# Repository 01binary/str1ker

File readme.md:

# Str1ker: The Drumming Mech

> [Str1ker](https://www.01binary.us/projects/drumming-robot/) is a human size, open-source mech integrated with Robot Operating System.

## Overview

Striker is a human-scale teleoperated mech built with metal casting, CNC machining, 3D printing, sheet metal parts, tube frame chassis, and pre-made components.

This open-source educational project features custom electronics and [Robot Operating System](https://www.ros.org/) integration, demonstrating how to design and build a large robot that combines mobility, sensing, and manipulation.

> See the [presentation](https://docs.google.com/presentation/d/125Y3McedITN_gVbnEh7SqTWY80QppUtimkaTmMLYEUg/edit?usp=sharing) about the robot at August 2026 [Portland Area Robotics Society](https://portlandrobotics.org/home.php?link_id=1) meeting.

| | | |
|-|-|-|
||||

The robot moves on a mecanum base, articulates its head and arms, and visualizes live lidar and RGB-D perception in Robot Visualization tool ([RViz](https://wiki.ros.org/rviz/Tutorials)).

The arms terminate in percussive end-effectors, designed for future live drum performance.

More details on [my blog](https://www.01binary.us/projects/drumming-robot/) and media on [instagram](https://www.instagram.com/01binaryus/). Say hello at the next [Portland Area Robotics Society](https://portlandrobotics.org/home.php?link_id=1) monthly meetup!

## Details

### Mechanical Design

[Autodesk Inventor mechanical parts](./cad) available in `./cad`.

### Electrical Design

[KiCad schematics and boards](./boards/) available in `./boards`.

### Fabrication

The arms were cast out of Aluminum 356 in the metal foundry at [Ctrl^H Hackerspace](https://pdxhackerspace.org/index.html) and welded together by [skorndaap](https://www.instagram.com/skorndaap/), then polished.

Tube frame chassis welding by [skorndaap](https://www.instagram.com/skorndaap/).

The CNC, sheet metal, tube frame, and 3D-printed parts were ordered from [Xometry](https://www.xometry.com/) online service.

The PCB's were ordered from [JLCPCB](https://jlcpcb.com/) using JLCPCB KiCad plugin.

Pre-made components sourced from [GoBilda](https://www.gobilda.com/), [Pololu](https://www.pololu.com/), [McMaster-Carr](https://www.mcmaster.com/), [Robot Shop](https://www.robotshop.com/), and Amazon.

### Software

- [Ubuntu 20.04](https://wiki.ros.org/noetic/Installation/Ubunt)
- [ROS Noetic](https://wiki.ros.org/noetic)
- [MoveIt](https://moveit.ai/)
- [ROS Control](./src/hardware/hardware.h)
- [Inverse Kinematics solver](./src/plugins/)
- [PID controller](./src/drivers/arm/pid.h)
- [ROS](./src) and [ROS Serial](./src/drivers/) nodes

### Hardware

- [Teensy 4.0](https://www.sparkfun.com/teensy-4-0.html) MCUs for arms, body and legs
- [Weidian](https://www.amazon.com/dp/B0BTVN6V7W) industrial mini PC for high-level control
- [Intel NUC 11](https://www.amazon.com/dp/B09PRL9V2F) for teleoperation & simulation

## System Requirements

The high-level controllers (Ubuntu 20.04/ROS Noetic) can run on any [mini PC](https://www.amazon.com/s?k=mini+pc), [NUC](https://www.amazon.com/s?k=NUC), a low-end Single Board Computer (SBC) like [Raspberry Pi](https://www.amazon.com/Raspberry-Model-2019-Quad-Bluetooth/dp/B07TD43PDZ/) or a high-end SBC like [Latte Panda 3 Delta](https://www.amazon.com/LattePanda-864-Pocket-Sized-Windows-Single-Computer/dp/B0C6TCP3MN).

The low-level serial nodes that run motors and sensors were designed for Arduino Mega, and are currently being ported to [Teensy 4.0](https://www.sparkfun.com/teensy-4-0.html) because its more powerful specs make it a better choice for robotics.

Teleoperation and simulation requires 3D visualization software like [RViz](https://wiki.ros.org/rviz) and [Gazebo](https://gazebosim.org/home), which [like NVidia cards](https://wiki.ros.org/simulator_gazebo/SystemRequirements).

## Setup

Follow the [official guide](https://wiki.ros.org/noetic/Installation/Ubuntu) to install ROS Noetic and [configure the ROS environment](https://wiki.ros.org/ROS/Tutorials/InstallingandConfiguringROSEnvironment).

Clone the projects:

```
mkdir -p ~/catkin_ws/src
cd ~/catkin_ws/src

git clone https://github.com/01binary/str1ker.git
git clone https://github.com/01binary/str1ker_moveit_config.git

cd ./str1ker
git sparse-checkout init --cone
git sparse-checkout set .vscode src config launch description msg
```

## Install Packages from Source

Follow the [official guide](https://moveit.ai/install/source/) to build MoveIt from source using `catkin_ws` as the workspace name instead of `moveit_ws`.

Prepare Gazebo plugins to be built from source:

```
cd ~/catkin_ws/src
git clone https://github.com/roboticsgroup/roboticsgroup_gazebo_plugins
```

## Install Packages

```
cd ~/catkin_ws/src
rosdep install -y --from-paths . --ignore-src --rosdistro noetic
```

## Build

To invoke the build command while in `~/catkin_ws` use `catkin_make` with no parameters. Otherwise use `-C` to specify the workspace directory:

```
catkin_make -C ~/catkin_ws
```

To build only this package and its dependencies:

```
catkin_make --only-pkg-with-deps str1ker
```

To build only this package:

```
catkin_make --pkg str1ker
```

To clear the build filter:

```
catkin_make -DCATKIN_WHITELIST_PACKAGES=""
```

To switch between Debug and Release

```
catkin_make -DCMAKE_BUILD_TYPE=Debug | Release
```

## Environment

One-time setup after the first build.

```
catkin_make install
source /opt/ros/noetic/setup.bash

echo "source /opt/ros/noetic/setup.bash" >> ~/.bashrc
source ~/.bashrc
```

## Upload

The low-level hardware is handled by an Arduino ROS node in `src/drivers/arm.ino`.

To build it, first generate ROS message headers for Arduino:

```
sudo apt-get install ros-${ROS_DISTRO}-rosserial-arduino
sudo apt-get install ros-${ROS_DISTRO}-rosserial

rosrun rosserial_arduino make_libraries.py ~/Arduino/libraries
```

> If you installed Arduino IDE as a *snap* plugin, Arduino libraries are likely in `~/snap/arduino` (the exact location is specific to your system).

Compile and upload the ROS node. The default launch configuration in `robot.launch` will connect to `/dev/ttyACM0` automatically.

### VSCode + Arduino CLI

This workspace includes VSCode tasks for compiling and uploading the Teensy firmware without Arduino IDE 2.

Install `arduino-cli`:

```bash
curl -fsSL https://raw.githubusercontent.com/arduino/arduino-cli/master/install.sh | BINDIR="$HOME/.local/bin" sh
arduino-cli version
```

Then in VSCode:

1. Open the Command Palette and run `C/C++: Select a Configuration...`
2. Pick `Arduino Teensy 4.0`
3. Run `Tasks: Run Task`
4. Use `Arduino: Compile Arm` or `Arduino: Upload Arm`

The checked-in VSCode configuration targets `teensy:avr:teensy40` on `/dev/ttyACM0` and uses the PJRC package index through `.vscode/arduino-cli.yaml`.

## Launch

### Hardware

To launch only the serial bridge to the arm firmware:

```
roslaunch str1ker arms.launch
```

To launch only the serial bridge to the main board firmware:

```
roslaunch str1ker main.launch
```

### Controllers

To launch ROS control nodes (URDF + controllers + state publisher):

```
roslaunch str1ker controllers.launch
```

### Full Stack

To launch both high-level and low-level nodes:

```
roslaunch str1ker robot.launch
```

### PrimeSense Carmine 1.09

To launch Carmine with OpenNI2 (recommended on ROS Noetic):

```
roslaunch str1ker vision.launch
```

To use legacy OpenNI instead:

```
roslaunch str1ker vision.launch use_openni2:=false
```

### Laser Scanner (Hokuyo UTM-30LX)

Install the Hokuyo ROS driver:

```
sudo apt-get install -y ros-${ROS_DISTRO}-urg-node
```

The default launch path uses the stable built-in udev symlink under `/dev/serial/by-id`.

If you still want a custom short alias (for example `/dev/str1ker_laser`), create one with:

```
# Example when Hokuyo appears as /dev/ttyACM0
./scripts/alias.sh /dev/ttyACM0 str1ker_laser --install
```

To launch the laser scanner driver:

```
roslaunch str1ker laserscan.launch
```

If you want to bypass by-id and use the current kernel device path:

```
roslaunch str1ker laserscan.launch serial_port:=/dev/ttyACM0
```

### Mecanum Legs

The legs firmware runs as a rosserial Arduino node and subscribes to `cmd_vel`
using `geometry_msgs/Twist` (`linear.x`, `linear.y`, and `angular.z`).

To launch the serial bridge:

```
roslaunch str1ker legs.launch serial_port:=/dev/ttyACM0
```

Quick forward-motion smoke test:

```
rostopic pub -r 10 /cmd_vel geometry_msgs/Twist "{linear: {x: 0.2, y: 0.0, z: 0.0}, angular: {x: 0.0, y: 0.0, z: 0.0}}"
```

### Teleoperation

To teleoperate the robot:

```
roslaunch str1ker_moveit_config demo.launch
```

### Simulation

To simulate the robot:

```
roslaunch str1ker_moveit_config gazebo.launch
```

### Configuration

The low-level configuration is in YAML format at [config](./config/).

To launch the MoveIt wizard for custom robot arm setup:

```
roslaunch moveit_setup_assistant setup_assistant.launch
```

## Logging

Logging level can be specified in `$ROS_ROOT/config/rosconsole.config`, either globally or for a specific package.

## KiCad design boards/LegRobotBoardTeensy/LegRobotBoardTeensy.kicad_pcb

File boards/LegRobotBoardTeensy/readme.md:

# Leg Robot Board

A board that controls the mobile platform with four mecanum wheels:

+ Leg Actuators
+ Leg Actuator Potentiometers
+ Leg Wheels
+ Leg Wheel Encoders
+ 9-DOF IMU
+ Enabled and PWM activity LEDs
+ Wheel Speed 7-Segment LED Indicators

## Modules

The following components are placed onto the board as modules:

|Module|Function|
|-|-|
|[Teensy 4.1](https://www.pjrc.com/store/teensy41.html)|[ROS](https://www.ros.org/) Node|
|[Adafruit 9-DOF IMU](https://www.adafruit.com/product/2472)|[TF2](https://wiki.ros.org/tf2) Transform|

## Devices

The following external components are connected to the board via `JST-XH` locking connectors:

|Device|Function|
|-|-|
|8x [IBT2 Motor Drivers](https://www.amazon.com/2-Piece-High-Power-Limiting-Function-Suitable/dp/B0DXKXKYRK)|Wheel Motor Drivers, Leg Actuator Drivers (`8` pin IDC connector: `3V3`, `GND`, `L_EN`, `R_EN`, `LPWM`, `RPWM`, `L_IS`, `R_IS`)|
|4x [Feedback Rod Linear Actuator](https://www.firgelliauto.com/products/feedback-rod-actuator?variant=2632742851) Potentiometers|Leg Actuator Potentiometers (`3` pin JST-XH connector: `3V3`, `SIG`, `GND`)|
|4x [Leg (Wheel) Encoder Board](../LegEncoderBoard/readme.md)|Wheel Encoders (`8` pin IDC connector: `A`, `B`, `I`, `3V3`, and four `GND`'s|

## Functionality

### PWM

There are four legs and each has two motors: a linear lift actuator and a brushed DC motor that runs the wheel.

Each PWM channel gets its own `EN` (Enabled) signal. The current sense signals (`L_IS`, `R_IS`) are included in the connector layout and sent over the wire, but not used anywhere on the board because there aren't enough pins for them. A multiplexer can be added later if the signals are desired.

### ADC

The linear lift actuators have built-in multi-turn potentiometers. These are routed to Teensy `ADC` pins.

### Quadrature

The [wheel encoders](../LegEncoderBoard/readme.md) are connected to each of the four wheels, outputting `A`, `B`, and `I` pulses counting rotations (`1000` pulses per revolution).

### Number Displays

Four 7-segment common anode LED number displays with decimal points display the speed of each wheel from `0.0` to `1.0`. They are driven by an LED multiplexer.

The LED multiplexer is mapped to four 2-digit LED displays with decimal point as follows:

| Display function                 | `IS31FL3730` pins |
| -------------------------------- | ----------------- |
| Digit common anodes              | `SW1–SW8`         |
| Segments A, B, C, D, E, F, G, DP | `CS1–CS8`         |

The [3621BH](https://www.amazon.com/uxcell-Common-Segment-Display-Digital/dp/B07GTRS9L2) common-anode LED displays have the following pin footprint:

| |1|2|3|4|5|
|-|-|-|-|-|-|
|1|`COM0`|`B`|`C`|`E`|`D`|
|2|`G`|`DP`|`A`|`F`|`COM1`|

The digit segments are mapped as follows:

|Digit|Segments
|-|-|
||`A` - Top of upper square<br>`F` - Left of upper square<br>`B` - Right of upper square<br>`G` - Link of both squares<br>`E` - Left of lower square<br>`C` - Right of lower square<br>`D` - Bottom of lower square<br>`DP` - Decimal point

## Pin Mapping

This board is essentially a shield. Labeled locking connectors are provided for all of the devices, PWM enabled/activity is indicated by LEDs, and wheel speeds are indicated by number displays.

| Pin            | Function                       | Group                     |
| -------------- | ------------------------------ | ------------------------- |
| `A16`          | Actuator 1 Potentiometer `SIG` | Front Left Leg (Actuator) |
| `D32`          | Quadrature Encoder 1 `A`       | Front Left Leg (Wheel)    |
| `D33`          | Quadrature Encoder 1 `B`       | Front Left Leg (Wheel)    |
| `D22`          | Quadrature Encoder 1 `Index`   | Front Left Leg (Wheel)    |
| `D26`          | Motor Driver 1 `EN`            | Front Left Leg (Wheel)    |
| `D27`          | Motor Driver 2 `EN`            | Front Left Leg (Actuator) |
| `D0`           | Motor Driver 1 `RPWM`          | Front Left Leg (Wheel)    |
| `D1`           | Motor Driver 1 `LPWM`          | Front Left Leg (Wheel)    |
| `D2`           | Motor Driver 2 `RPWM`          | Front Left Leg (Actuator) |
| `D3`           | Motor Driver 2 `LPWM`          | Front Left Leg (Actuator) |
| `A17`          | Actuator 2 Potentiometer `SIG` | Front Right Leg (Actuator)|
| `D34`          | Quadrature Encoder 2 `A`       | Front Right Leg (Wheel)   |
| `D35`          | Quadrature Encoder 2 `B`       | Front Right Leg (Wheel)   |
| `D23`          | Quadrature Encoder 2 `Index`   | Front Right Leg (Wheel)   |
| `D28`          | Motor Driver 3 `EN`            | Front Right Leg (Wheel)   |
| `D29`          | Motor Driver 4 `EN`            | Front Right Leg (Actuator)|
| `D4`           | Motor Driver 3 `RPWM`          | Front Right Leg (Wheel)   |
| `D5`           | Motor Driver 3 `LPWM`          | Front Right Leg (Wheel)   |
| `D6`           | Motor Driver 4 `RPWM`          | Front Right Leg (Actuator)|
| `D7`           | Motor Driver 4 `LPWM`          | Front Right Leg (Actuator)|
| `A2`           | Actuator 3 Potentiometer `SIG` | Rear Left Leg (Actuator)  |
| `D36`          | Quadrature Encoder 3 `A`       | Rear Left Leg (Wheel)     |
| `D37`          | Quadrature Encoder 3 `B`       | Rear Left Leg (Wheel)     |
| `D24`          | Quadrature Encoder 3 `Index`   | Rear Left Leg (Wheel)     |
| `D30`          | Motor Driver 5 `EN`            | Rear Left Leg (Wheel)     |
| `D31`          | Motor Driver 6 `EN`            | Rear Left Leg (Actuator)  |
| `D8`           | Motor Driver 5 `RPWM`          | Rear Left Leg (Wheel)     |
| `D9`           | Motor Driver 5 `LPWM`          | Rear Left Leg (Wheel)     |
| `D10`          | Motor Driver 6 `RPWM`          | Rear Left Leg (Actuator)  |
| `D11`          | Motor Driver 6 `LPWM`          | Rear Left Leg (Actuator)  |
| `A3`           | Actuator 4 Potentiometer `SIG` | Rear Right Leg (Actuator) |
| `D38`          | Quadrature Encoder 4 `A`       | Rear Right Leg (Wheel)    |
| `D39`          | Quadrature Encoder 4 `B`       | Rear Right Leg (Wheel)    |
| `D25`          | Quadrature Encoder 4 `Index`   | Rear Right Leg (Wheel)    |
| `D20`          | Motor Driver 7 `EN`            | Rear Right Leg (Wheel)    |
| `D21`          | Motor Driver 8 `EN`            | Rear Right Leg (Actuator) |
| `D12`          | Motor Driver 7 `RPWM`          | Rear Right Leg (Wheel)    |
| `D13`          | Motor Driver 7 `LPWM`          | Rear Right Leg (Wheel)    |
| `D14`          | Motor Driver 8 `RPWM`          | Rear Right Leg (Actuator) |
| `D15`          | Motor Driver 8 `LPWM`          | Rear Right Leg (Actuator) |
| `A5`           | I2C `SCL`                      | IMU, LED Driver           |
| `A4`           | I2C `SDA`                      | IMU, LED Driver           |

## Buses

|Device|Bus|Address
|-|-|-|
|IMU|I2C|`0x28` (`ADR` tied to `GND` to set address)|
|IS31FL3730|I2C|`0x74`|

## Bill of Materials

|Component|Description|
|-|-|
|[IS31FL3730](https://www.digikey.com/en/products/detail/lumissil-microsystems/IS31FL3730-QFLS2-TR/5319756)|LED Driver/Multiplexer
|[CL3621BH](https://www.amazon.com/dp/B07GTQTD8S)|LED Displays (2-Digit, 7-Segment, 10-Pin Common Anode) for Wheel Speeds
|[XL-1608SURC-06](https://www.lcsc.com/product-detail/C965799.html)|Red LED for `EN` signals|
|[150080BS75000](https://www.digikey.com/en/products/detail/w%C3%BCrth-elektronik/)|Blue LED for `LPWM`/`RPWM` signals|
|[RC0603FR-07150RL](https://www.digikey.com/en/products/detail/yageo/RC0603FR-07150RL/726958)|`150 Ohm` LED Resistor|
|[RC0603FR-07470RL](https://www.digikey.com/en/products/detail/yageo/RC0603FR-07470RL/727256)|`470R` Red LED Resistor|
|[RCG06031K00FKEA](https://www.digikey.com/en/products/detail/vishay-dale/rcg06031k00fkea/4172389)|`1K` LED Resistor|
|[RC0603FR-072K2L](https://www.digikey.com/en/products/detail/yageo/rc0603fr-072k2l/727016)|`2.2K` Series Resistor (ADC channels)|
|[CR0603-FX-4701ELF](https://www.digikey.com/en/products/detail/bourns-inc/cr0603-fx-4701elf/3740916)|`4.7K` Pull-Up Resistor for LED Multiplexer|
|[CRCW060310K0FKEA](https://www.digikey.com/en/products/detail/vishay-dale/crcw060310k0fkea/1174782)|`10K` 555 Timer Pull-Up Resistor, Transistor Base Resistor|
|[HoAR0603-1/10W-20KR-1%-TCR25](https://jlcpcb.com/partdetail/C5123585)|`20K` LED Driver Current Setting Resistor|
|[CRCW0603100KFKEA](https://www.digikey.com/en/products/detail/vishay-dale/crcw0603100kfkea/1174896)|`100K` Transistor Base Pull-Down Resistor|
|[RC0603FR-07360KL](https://www.digikey.com/en/products/detail/yageo/rc0603fr-07360kl/727183)|`360K` 555 Timer Resistor|
|[C0402C103J4RACTU](https://www.digikey.com/en/products/detail/kemet/C0402C103J4RACTU/411041)|`10nF` 555 Timer Capacitor|
|[CL10B473KB8NNNC](https://www.digikey.com/en/products/detail/samsung-electro-mechanics/cl10b473kb8nnnc/3886721)|`47nF` Decoupling Capacitor (ADC channels)|
|[CC0603KRX7R9BB104](https://www.digikey.com/en/products/detail/yageo/cc0603krx7r9bb104/2103082)|`100nF` IMU Capacitor|
|[CC0603JRX7R7BB105](https://www.digikey.com/en/products/detail/yageo/CC0603JRX7R7BB105/7164369)|`1uF` 555 Timer Capacitor|
|[SN74HC08DR](https://www.digikey.com/en/products/detail/texas-instruments/sn74hc08dr/276834)|IC Gate|
|[MMBT3904LT1G](https://www.digikey.com/en/products/detail/onsemi/MMBT3904LT1G/919601)|LED Transistor|
|[TLC555CDR](https://www.digikey.com/en/products/detail/texas-instruments/tlc555cdr/276979)|555 Timer|
|[JST_XH_B3B-XH-A](https://www.digikey.com/en/products/detail/jst-sales-america-inc/b3b-xh-a/1651046)|Actuator Potentiometers (`3V3`, `SIG`, `GND`)|
|[Molex 0702460802](https://www.digikey.com/en/products/detail/molex/0702460802/760180)|Motor Drivers (`LPWM`, `RPWM`, `L_EN`, `R_EN`, `L_IS`, `R_IS`, `3V3`, `GND`)|
|[Teensy 4.1](https://www.sparkfun.com/teensy-4-1.html)|Teensy 4.1 without Headers|
|[ICM-648-1-GT-HT](https://www.digikey.com/en/products/detail/adam-tech/ICM-648-1-GT-HT/9832918)|Teensy IC DIP Socket, 48P|
|[Needle Headers](https://www.amazon.com/dp/B09WH8N3HX)|Teensy Needle Headers for DIP Socket|
|[DIP Socket 10 pin](https://www.amazon.com/dp/B0FVDT8JGV)|LED number displays IC socket

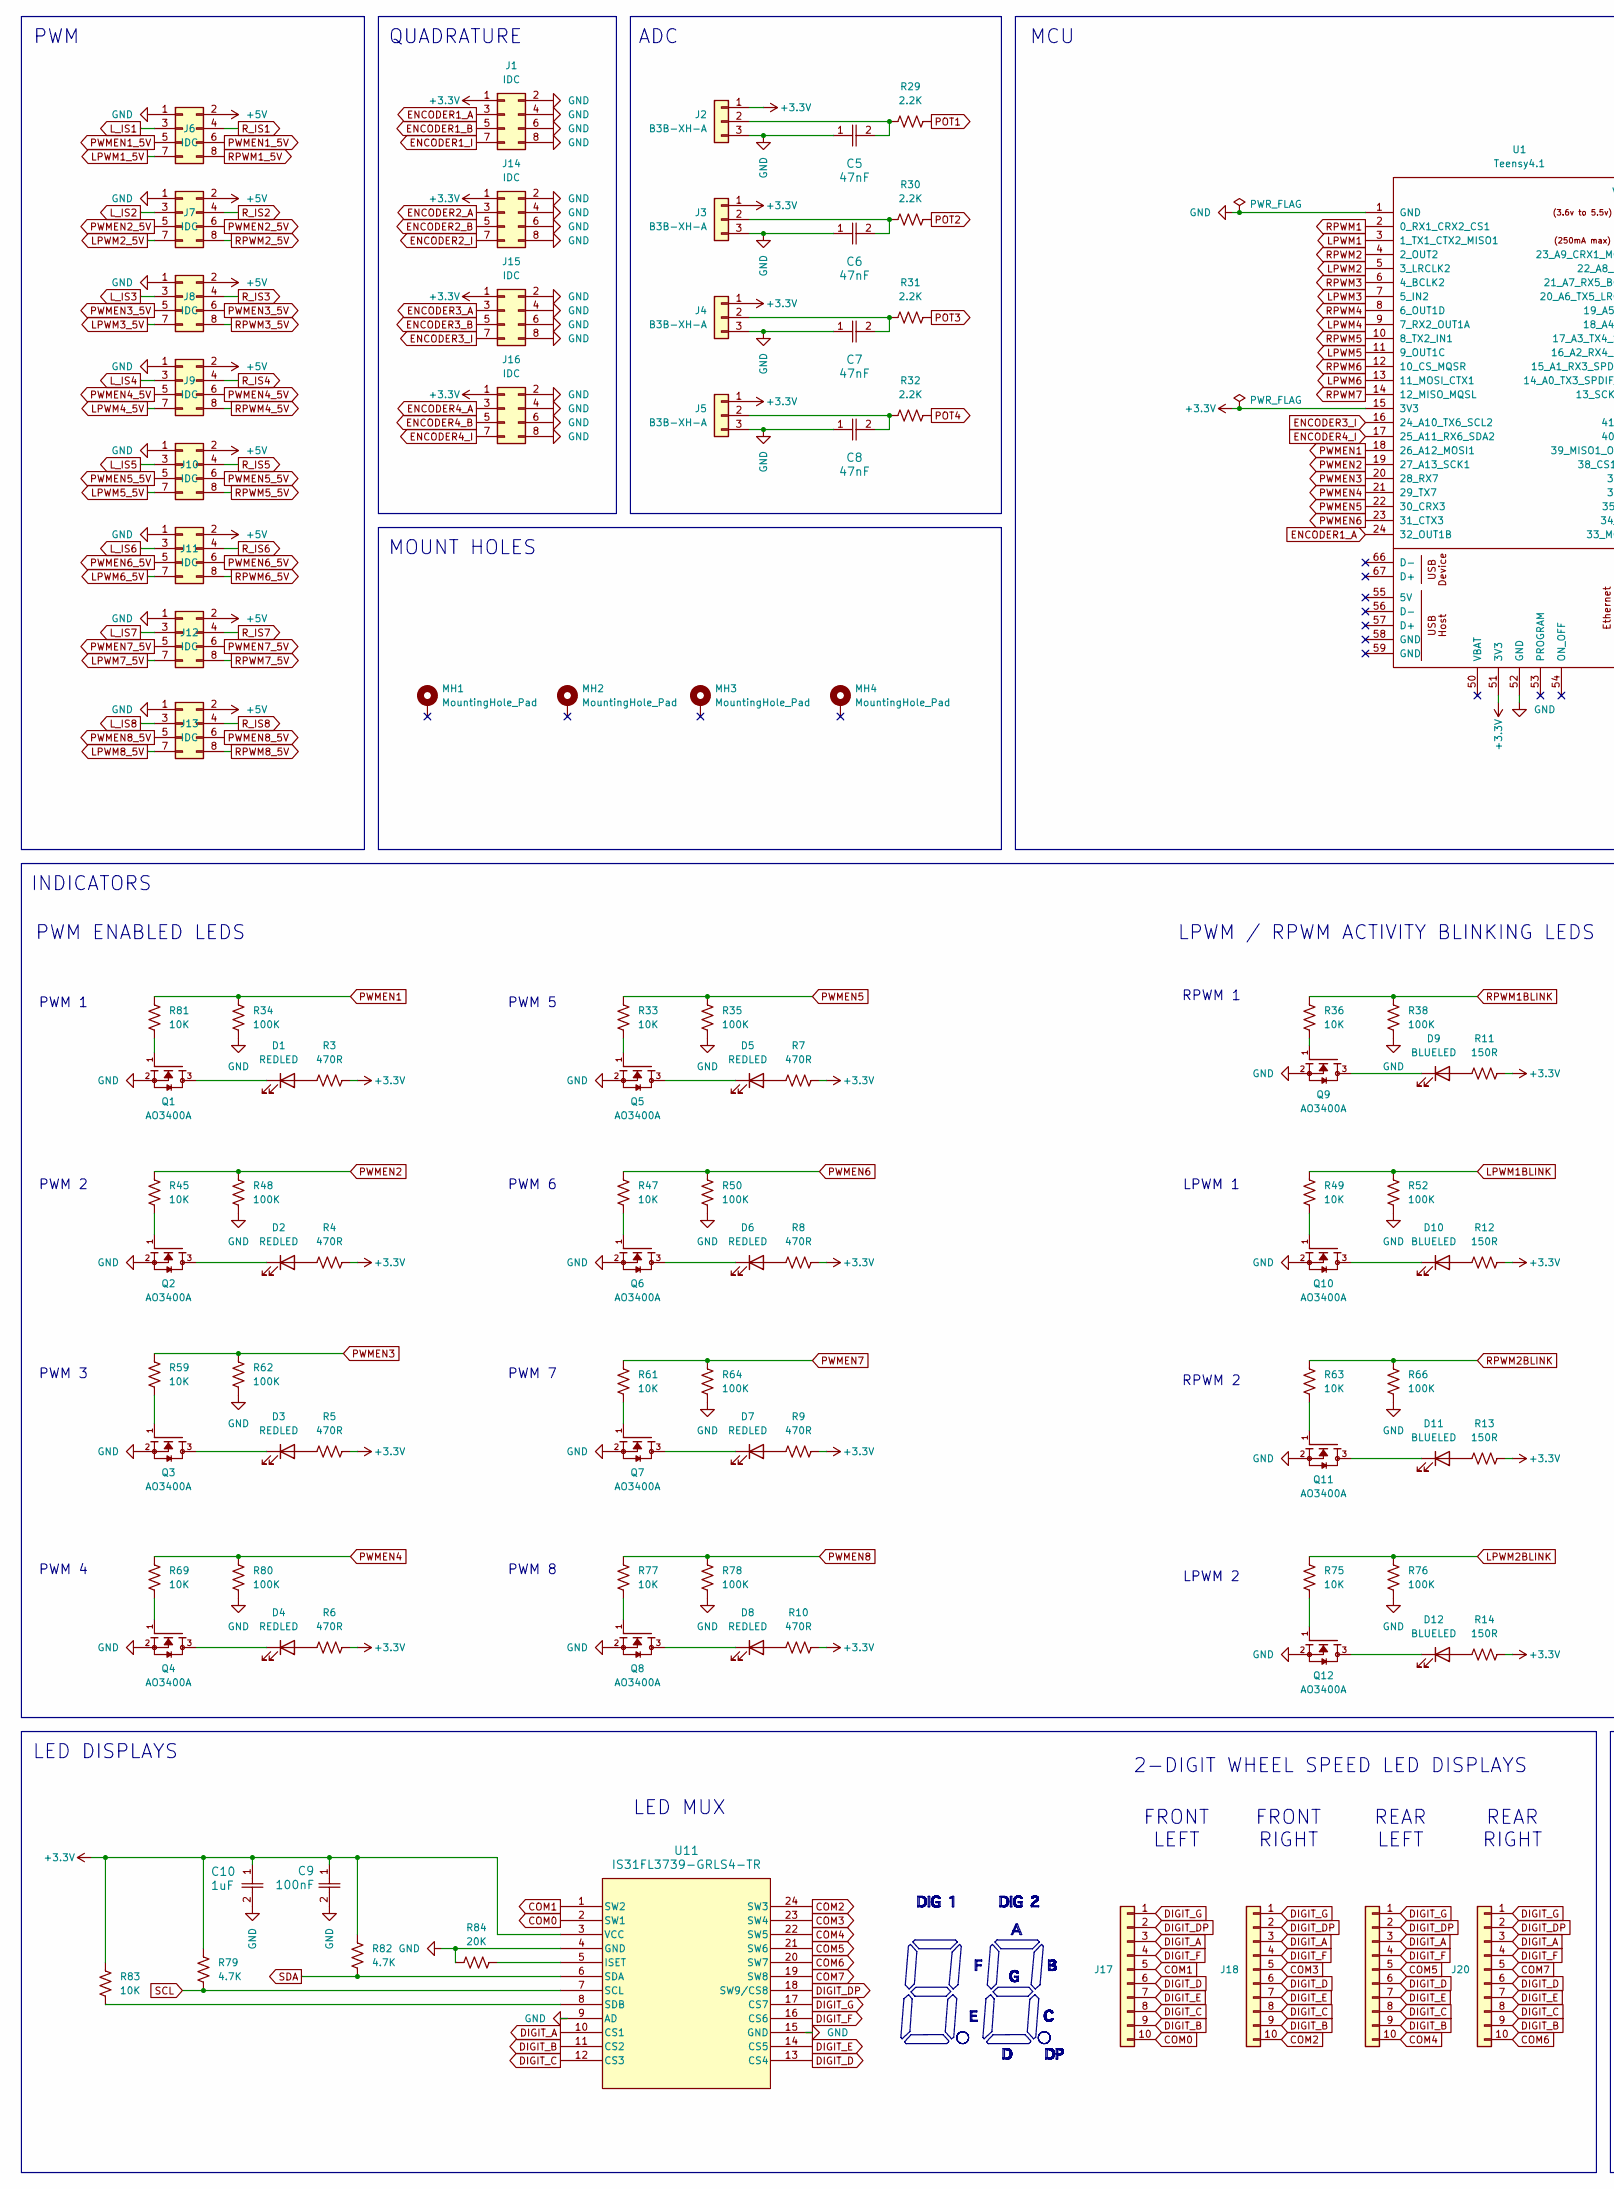
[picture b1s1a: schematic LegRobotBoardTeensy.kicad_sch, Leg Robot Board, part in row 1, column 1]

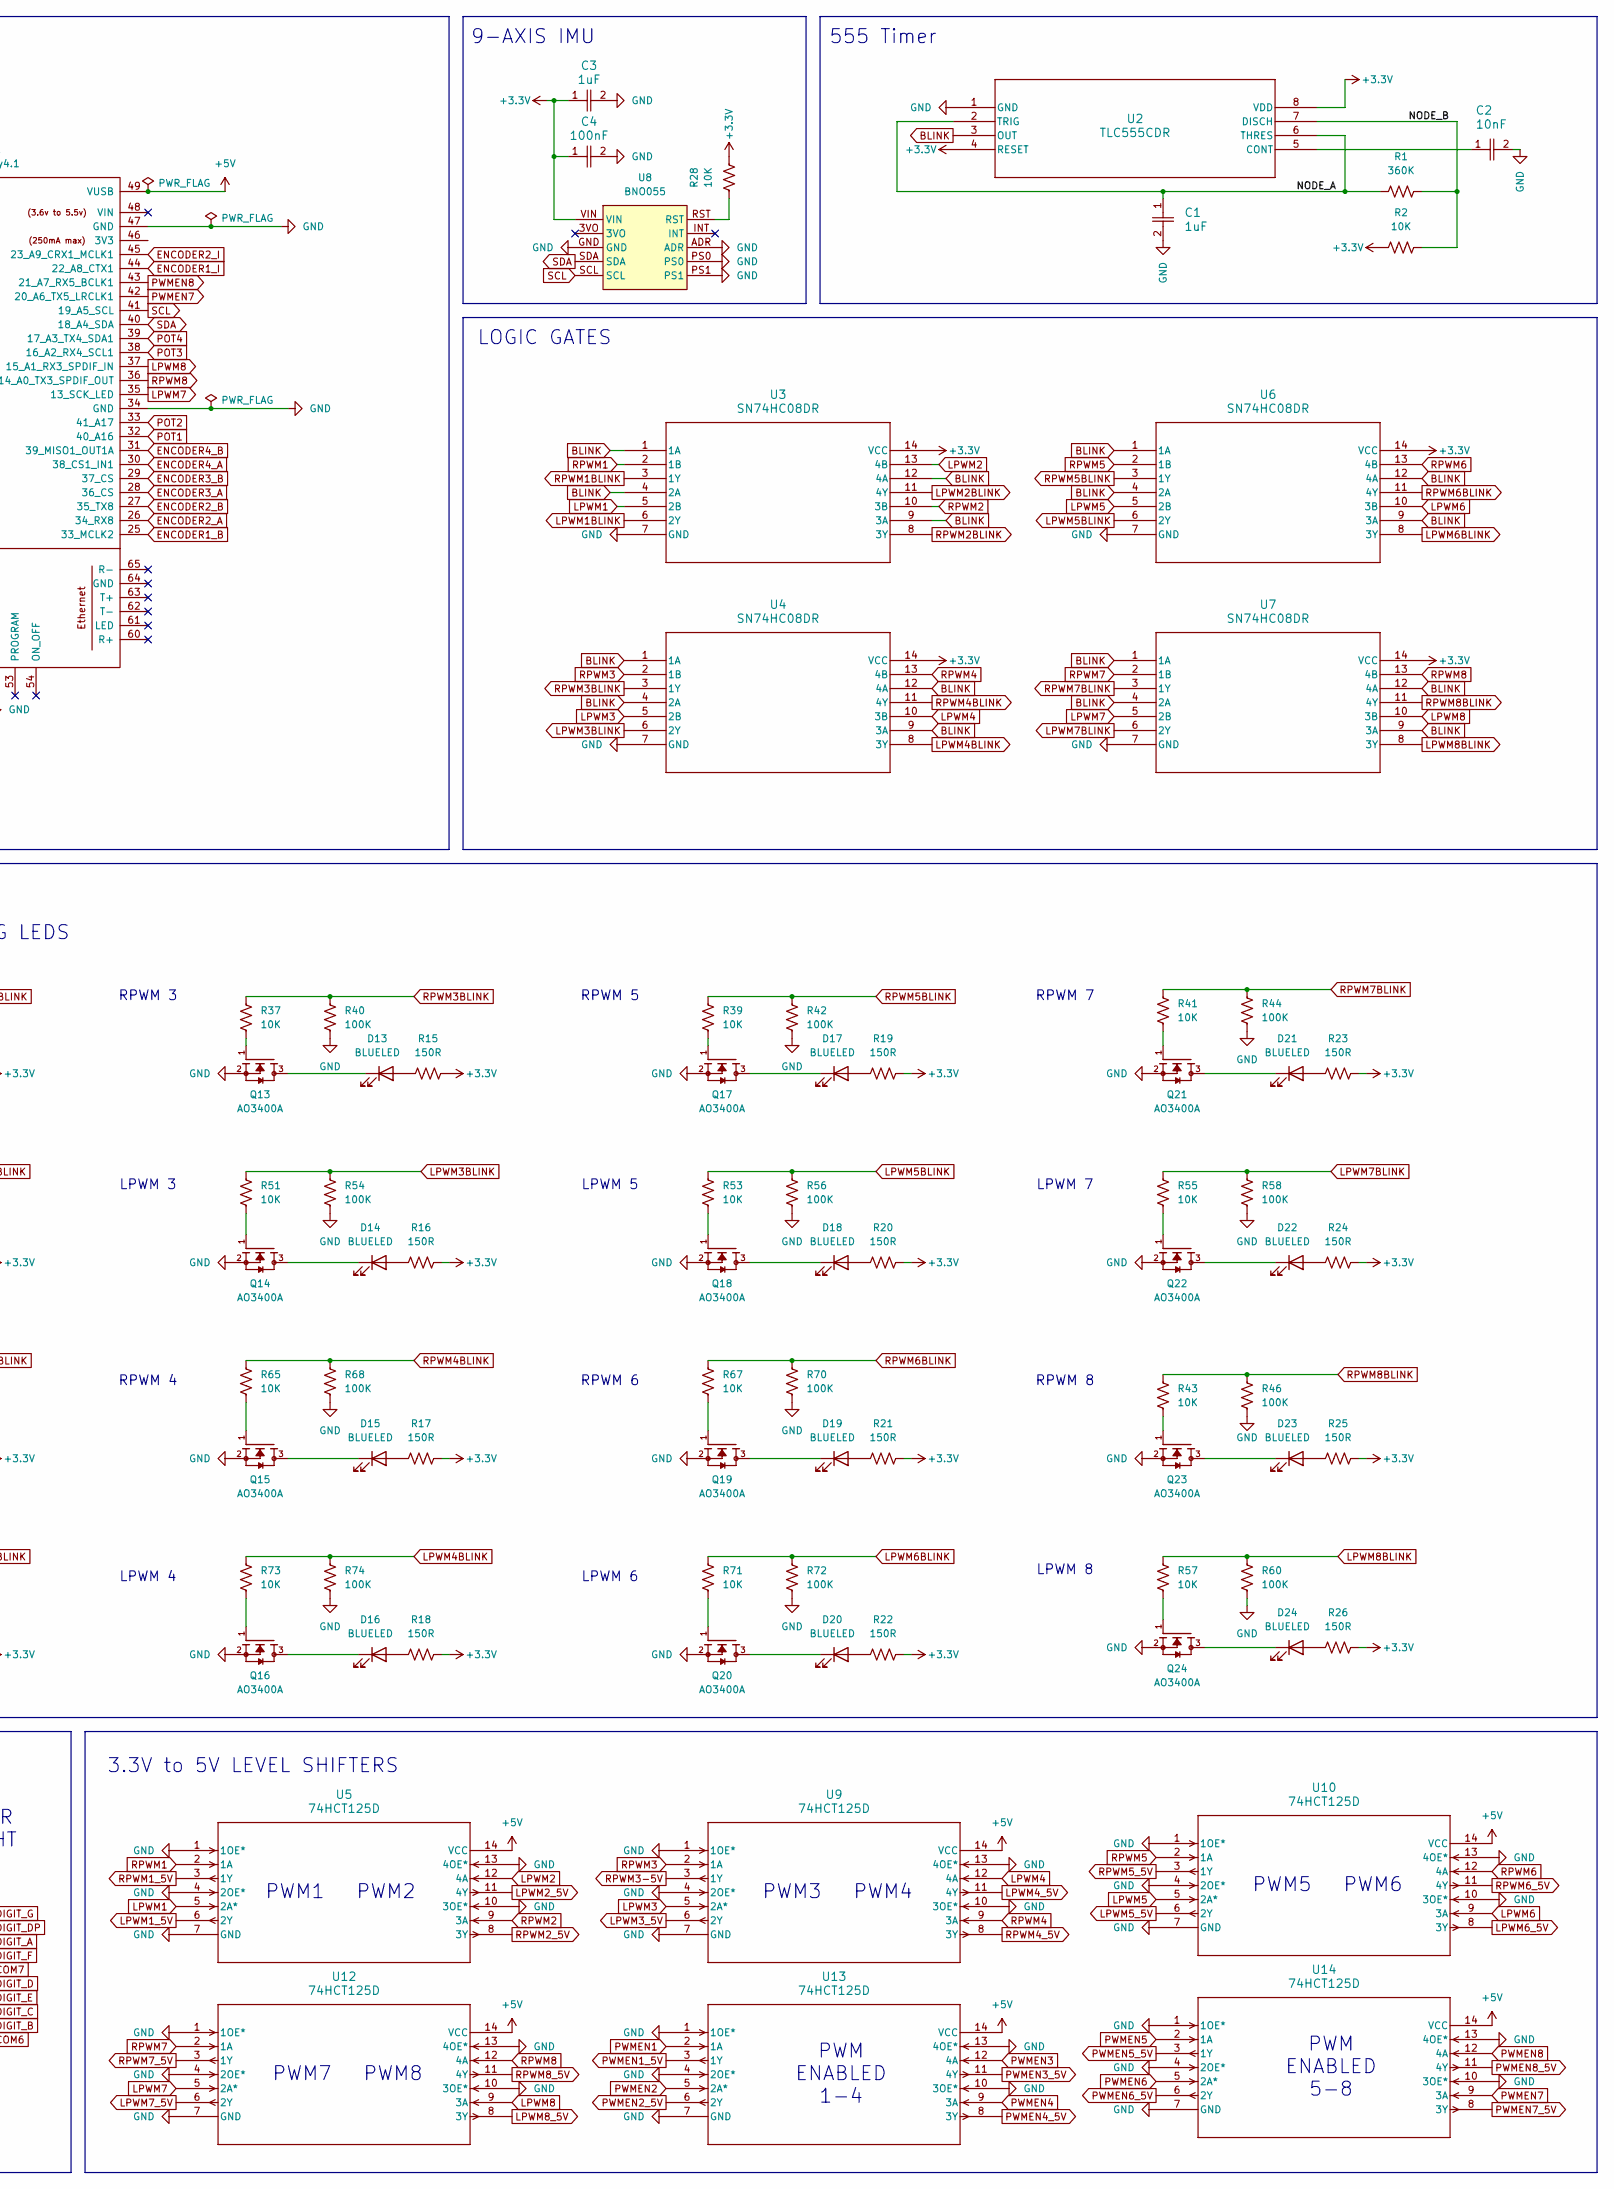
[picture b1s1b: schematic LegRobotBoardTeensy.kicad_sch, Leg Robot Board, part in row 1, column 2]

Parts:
C1, C3: 1uF; CC0603JRX7R7BB105; LCSC C519560
C2: 10nF; C0402C103J4RACTU; LCSC C2167451
C4, C9: 100nF; CC0603KRX7R9BB104; LCSC C14663
C5, C6, C7, C8: 47nF; CAPC1608X90N; LCSC C1622
C10: 1uF; CC0603JRX7R7BB105; LCSC C2167451
D1, D2, D3, D4, D5, D6, D7, D8: REDLED; XL-1608SURC-06; LCSC C965799
D9, D10, D11, D12, D13, D14, D15, D16, D17, D18, D19, D20, D21, D22, D23, D24: BLUELED; 150080BS75000_Modified; LCSC C6067133
J1, J6, J7, J8, J9, J10, J11, J12, J13, J14, J15, J16: IDC; IDC-Header_2x04_P2.54mm_Vertical
J2, J3, J4, J5: B3B-XH-A; JST_XH_B3B-XH-A_1x03_P2.50mm_Vertical
J17, J18, J19, J20: Conn_01x10; DIP-10_W10.16mm
MH1, MH2, MH3, MH4: MountingHole_Pad; MountingHole_3.2mm_M3_ISO7380_Pad
Q1, Q2, Q3, Q4, Q5, Q6, Q7, Q8, Q9, Q10, Q11, Q12, Q13, Q14, Q15, Q16, Q17, Q18, Q19, Q20, Q21, Q22, Q23, Q24: AO3400A; LCSC C20917
R1: 360K; RC0603FR-07360KL; LCSC C137740
R2, R28, R33, R36, R37, R39, R41, R43, R45, R47, R49, R51, R53, R55, R57, R59, R61, R63, R65, R67, R69, R71, R73, R75, R77, R81, R83: 10K; CRCW060310K0FKEA; LCSC C844918
R3, R4, R5, R6, R7, R8, R9, R10: 470R; RC0603FR-07470RL; LCSC C114669
R11, R12, R13, R14, R15, R16, R17, R18, R19, R20, R21, R22, R23, R24, R25, R26: 150R; RESC1607X60N; LCSC C114608
R29, R30, R31, R32: 2.2K; RC0603FR-072K2L; LCSC C114662
R34, R35, R38, R40, R42, R44, R46, R48, R50, R52, R54, R56, R58, R60, R62, R64, R66, R68, R70, R72, R74, R76, R78, R80: 100K; CRCW0603100KFKEA; LCSC C844916
R79, R82: 4.7K; CR0603-FX-4701ELF; LCSC C17673
R84: 20K; CRCW060310K0FKEA; LCSC C5123585
U1: Teensy4.1; Teensy41
U2: TLC555CDR; LCSC C6986
U3, U4, U6, U7: SN74HC08DR; LCSC C337768
U5, U9, U10, U12, U13, U14: 74HCT125D; LCSC C5962
U8: BNO055
U11: IS31FL3739-GRLS4-TR; IS31FL3730-QFLS2-TR

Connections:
+3.3V: C3.1, C4.1, C9.1, C10.1, J1.1, J2.1, J3.1, J4.1, J5.1, J14.1, J15.1, J16.1, R2.1, R3.2, R4.2, R5.2, R6.2, R7.2, R8.2, R9.2, R10.2, R11.2, R12.2, R13.2, R14.2, R15.2, R16.2, R17.2, R18.2, R19.2, R20.2, R21.2, R22.2, R23.2, R24.2, R25.2, R26.2, R28.2, R79.1, R82.1, R83.1, U1.15 (3V3), U1.51 (3V3), U2.4 (RESET), U2.8 (VDD), U3.14 (VCC), U4.14 (VCC), U6.14 (VCC), U7.14 (VCC), U8.VIN, U11.3 (VCC)
+5V: J6.2, J7.2, J8.2, J9.2, J10.2, J11.2, J12.2, J13.2, U1.49 (VUSB), U5.14 (VCC), U9.14 (VCC), U10.14 (VCC), U12.14 (VCC), U13.14 (VCC), U14.14 (VCC)
/NODE_A: C1.1, R1.1, U2.2 (TRIG), U2.6 (THRES)
/NODE_B: R1.2, R2.2, U2.7 (DISCH)
BLINK: U2.3 (OUT), U3.1 (1A), U3.4 (2A), U3.9 (3A), U3.12 (4A), U4.1 (1A), U4.4 (2A), U4.9 (3A), U4.12 (4A), U6.1 (1A), U6.4 (2A), U6.9 (3A), U6.12 (4A), U7.1 (1A), U7.4 (2A), U7.9 (3A), U7.12 (4A)
COM0: J17.10, U11.2 (SW1)
COM1: J17.5, U11.1 (SW2)
COM2: J18.10, U11.24 (SW3)
COM3: J18.5, U11.23 (SW4)
COM4: J19.10, U11.22 (SW5)
COM5: J19.5, U11.21 (SW6)
COM6: J20.10, U11.20 (SW7)
COM7: J20.5, U11.19 (SW8)
DIGIT_A: J17.3, J18.3, J19.3, J20.3, U11.10 (CS1)
DIGIT_B: J17.9, J18.9, J19.9, J20.9, U11.11 (CS2)
DIGIT_C: J17.8, J18.8, J19.8, J20.8, U11.12 (CS3)
DIGIT_D: J17.6, J18.6, J19.6, J20.6, U11.13 (CS4)
DIGIT_DP: J17.2, J18.2, J19.2, J20.2, U11.18 (SW9/CS8)
DIGIT_E: J17.7, J18.7, J19.7, J20.7, U11.14 (CS5)
DIGIT_F: J17.4, J18.4, J19.4, J20.4, U11.16 (CS6)
DIGIT_G: J17.1, J18.1, J19.1, J20.1, U11.17 (CS7)
ENCODER1_A: J1.3, U1.24 (32_OUT1B)
ENCODER1_B: J1.5, U1.25 (33_MCLK2)
ENCODER1_I: J1.7, U1.44 (22_A8_CTX1)
ENCODER2_A: J14.3, U1.26 (34_RX8)
ENCODER2_B: J14.5, U1.27 (35_TX8)
ENCODER2_I: J14.7, U1.45 (23_A9_CRX1_MCLK1)
ENCODER3_A: J15.3, U1.28 (36_CS)
ENCODER3_B: J15.5, U1.29 (37_CS)
ENCODER3_I: J15.7, U1.16 (24_A10_TX6_SCL2)
ENCODER4_A: J16.3, U1.30 (38_CS1_IN1)
ENCODER4_B: J16.5, U1.31 (39_MISO1_OUT1A)
ENCODER4_I: J16.7, U1.17 (25_A11_RX6_SDA2)
GND: C1.2, C2.2, C3.2, C4.2, C5.1, C6.1, C7.1, C8.1, C9.2, C10.2, J1.2, J1.4, J1.6, J1.8, J2.3, J3.3, J4.3, J5.3, J6.1, J7.1, J8.1, J9.1, J10.1, J11.1, J12.1, J13.1, J14.2, J14.4, J14.6, J14.8, J15.2, J15.4, J15.6, J15.8, J16.2, J16.4, J16.6, J16.8, Q1.2, Q2.2, Q3.2, Q4.2, Q5.2, Q6.2, Q7.2, Q8.2, Q9.2, Q10.2, Q11.2, Q12.2, Q13.2, Q14.2, Q15.2, Q16.2, Q17.2, Q18.2, Q19.2, Q20.2, Q21.2, Q22.2, Q23.2, Q24.2, R34.2, R35.2, R38.2, R40.2, R42.2, R44.2, R46.2, R48.2, R50.2, R52.2, R54.2, R56.2, R58.2, R60.2, R62.2, R64.2, R66.2, R68.2, R70.2, R72.2, R74.2, R76.2, R78.2, R80.2, R84.1, U1.1 (GND), U1.34 (GND), U1.47 (GND), U1.52 (GND), U2.1 (GND), U3.7 (GND), U4.7 (GND), U5.1 (1OE*), U5.4 (2OE*), U5.7 (GND), U5.10 (3OE*), U5.13 (4OE*), U6.7 (GND), U7.7 (GND), U8.ADR, U8.GND, U8.PS0, U8.PS1, U9.1 (1OE*), U9.4 (2OE*), U9.7 (GND), U9.10 (3OE*), U9.13 (4OE*), U10.1 (1OE*), U10.4 (2OE*), U10.7 (GND), U10.10 (3OE*), U10.13 (4OE*), U11.4 (GND), U11.9 (AD), U11.15 (GND), U12.1 (1OE*), U12.4 (2OE*), U12.7 (GND), U12.10 (3OE*), U12.13 (4OE*), U13.1 (1OE*), U13.4 (2OE*), U13.7 (GND), U13.10 (3OE*), U13.13 (4OE*), U14.1 (1OE*), U14.4 (2OE*), U14.7 (GND), U14.10 (3OE*), U14.13 (4OE*)
LPWM1: U1.3 (1_TX1_CTX2_MISO1), U3.5 (2B), U5.5 (2A*)
LPWM1BLINK: R49.1, R52.1, U3.6 (2Y)
LPWM1_5V: J6.7, U5.6 (2Y)
LPWM2: U1.5 (3_LRCLK2), U3.13 (4B), U5.12 (4A)
LPWM2BLINK: R75.1, R76.1, U3.11 (4Y)
LPWM2_5V: J7.7, U5.11 (4Y)
LPWM3: U1.7 (5_IN2), U4.5 (2B), U9.5 (2A*)
LPWM3BLINK: R51.1, R54.1, U4.6 (2Y)
LPWM3_5V: J8.7, U9.6 (2Y)
LPWM4: U1.9 (7_RX2_OUT1A), U4.10 (3B), U9.12 (4A)
LPWM4BLINK: R73.1, R74.1, U4.8 (3Y)
LPWM4_5V: J9.7, U9.11 (4Y)
LPWM5: U1.11 (9_OUT1C), U6.5 (2B), U10.5 (2A*)
LPWM5BLINK: R53.1, R56.1, U6.6 (2Y)
LPWM5_5V: J10.7, U10.6 (2Y)
LPWM6: U1.13 (11_MOSI_CTX1), U6.10 (3B), U10.9 (3A)
LPWM6BLINK: R71.1, R72.1, U6.8 (3Y)
LPWM6_5V: J11.7, U10.8 (3Y)
LPWM7: U1.35 (13_SCK_LED), U7.5 (2B), U12.5 (2A*)
LPWM7BLINK: R55.1, R58.1, U7.6 (2Y)
LPWM7_5V: J12.7, U12.6 (2Y)
LPWM8: U1.37 (15_A1_RX3_SPDIF_IN), U7.10 (3B), U12.9 (3A)
LPWM8BLINK: R57.1, R60.1, U7.8 (3Y)
LPWM8_5V: J13.7, U12.8 (3Y)
L_IS1: J6.3
L_IS2: J7.3
L_IS3: J8.3
L_IS4: J9.3
L_IS5: J10.3
L_IS6: J11.3
L_IS7: J12.3
L_IS8: J13.3
unnamed: D1.2 (A), R3.1
unnamed: D1.1 (K), Q1.3
unnamed: D2.2 (A), R4.1
unnamed: D2.1 (K), Q2.3
unnamed: D3.2 (A), R5.1
unnamed: D3.1 (K), Q3.3
unnamed: D4.2 (A), R6.1
unnamed: D4.1 (K), Q4.3
unnamed: D5.2 (A), R7.1
unnamed: D5.1 (K), Q5.3
unnamed: D6.2 (A), R8.1
unnamed: D6.1 (K), Q6.3
unnamed: D7.2 (A), R9.1
unnamed: D7.1 (K), Q7.3
unnamed: D8.2 (A), R10.1
unnamed: D8.1 (K), Q8.3
unnamed: D9.2 (A), R11.1
unnamed: D9.1 (K), Q9.3
unnamed: D10.2 (A), R12.1
unnamed: D10.1 (K), Q10.3
unnamed: D11.2 (A), R13.1
unnamed: D11.1 (K), Q11.3
unnamed: D12.2 (A), R14.1
unnamed: D12.1 (K), Q12.3
unnamed: D13.2 (A), R15.1
unnamed: D13.1 (K), Q13.3
unnamed: D14.2 (A), R16.1
unnamed: D14.1 (K), Q14.3
unnamed: D15.2 (A), R17.1
unnamed: D15.1 (K), Q15.3
unnamed: D16.2 (A), R18.1
unnamed: D16.1 (K), Q16.3
unnamed: D17.2 (A), R19.1
unnamed: D17.1 (K), Q17.3
unnamed: D18.2 (A), R20.1
unnamed: D18.1 (K), Q18.3
unnamed: D19.2 (A), R21.1
unnamed: D19.1 (K), Q19.3
unnamed: D20.2 (A), R22.1
unnamed: D20.1 (K), Q20.3
unnamed: D21.2 (A), R23.1
unnamed: D21.1 (K), Q21.3
unnamed: D22.2 (A), R24.1
unnamed: D22.1 (K), Q22.3
unnamed: D23.2 (A), R25.1
unnamed: D23.1 (K), Q23.3
unnamed: D24.2 (A), R26.1
unnamed: D24.1 (K), Q24.3
unnamed: C5.2, J2.2, R29.1
unnamed: C6.2, J3.2, R30.1
unnamed: C7.2, J4.2, R31.1
unnamed: C8.2, J5.2, R32.1
unnamed: Q1.1, R81.2
unnamed: Q2.1, R45.2
unnamed: Q3.1, R59.2
unnamed: Q4.1, R69.2
unnamed: Q5.1, R33.2
unnamed: Q6.1, R47.2
unnamed: Q7.1, R61.2
unnamed: Q8.1, R77.2
unnamed: Q9.1, R36.2
unnamed: Q10.1, R49.2
unnamed: Q11.1, R63.2
unnamed: Q12.1, R75.2
unnamed: Q13.1, R37.2
unnamed: Q14.1, R51.2
unnamed: Q15.1, R65.2
unnamed: Q16.1, R73.2
unnamed: Q17.1, R39.2
unnamed: Q18.1, R53.2
unnamed: Q19.1, R67.2
unnamed: Q20.1, R71.2
unnamed: Q21.1, R41.2
unnamed: Q22.1, R55.2
unnamed: Q23.1, R43.2
unnamed: Q24.1, R57.2
unnamed: R28.1, U8.RST
unnamed: C2.1, U2.5 (CONT)
unnamed: R84.2, U11.5 (ISET)
unnamed: R83.2, U11.8 (SDB)
POT1: R29.2, U1.32 (40_A16)
POT2: R30.2, U1.33 (41_A17)
POT3: R31.2, U1.38 (16_A2_RX4_SCL1)
POT4: R32.2, U1.39 (17_A3_TX4_SDA1)
PWMEN1: R34.1, R81.1, U1.18 (26_A12_MOSI1), U13.2 (1A)
PWMEN1_5V: J6.5, J6.6, U13.3 (1Y)
PWMEN2: R45.1, R48.1, U1.19 (27_A13_SCK1), U13.5 (2A*)
PWMEN2_5V: J7.5, J7.6, U13.6 (2Y)
PWMEN3: R59.1, R62.1, U1.20 (28_RX7), U13.12 (4A)
PWMEN3_5V: J8.5, J8.6, U13.11 (4Y)
PWMEN4: R69.1, R80.1, U1.21 (29_TX7), U13.9 (3A)
PWMEN4_5V: J9.5, J9.6, U13.8 (3Y)
PWMEN5: R33.1, R35.1, U1.22 (30_CRX3), U14.2 (1A)
PWMEN5_5V: J10.5, J10.6, U14.3 (1Y)
PWMEN6: R47.1, R50.1, U1.23 (31_CTX3), U14.5 (2A*)
PWMEN6_5V: J11.5, J11.6, U14.6 (2Y)
PWMEN7: R61.1, R64.1, U1.42 (20_A6_TX5_LRCLK1), U14.9 (3A)
PWMEN7_5V: J12.5, J12.6, U14.8 (3Y)
PWMEN8: R77.1, R78.1, U1.43 (21_A7_RX5_BCLK1), U14.12 (4A)
PWMEN8_5V: J13.5, J13.6, U14.11 (4Y)
RPWM1: U1.2 (0_RX1_CRX2_CS1), U3.2 (1B), U5.2 (1A)
RPWM1BLINK: R36.1, R38.1, U3.3 (1Y)
RPWM1_5V: J6.8, U5.3 (1Y)
RPWM2: U1.4 (2_OUT2), U3.10 (3B), U5.9 (3A)
RPWM2BLINK: R63.1, R66.1, U3.8 (3Y)
RPWM2_5V: J7.8, U5.8 (3Y)
RPWM3: U1.6 (4_BCLK2), U4.2 (1B), U9.2 (1A)
RPWM3-5V: U9.3 (1Y)
RPWM3BLINK: R37.1, R40.1, U4.3 (1Y)
RPWM3_5V: J8.8
RPWM4: U1.8 (6_OUT1D), U4.13 (4B), U9.9 (3A)
RPWM4BLINK: R65.1, R68.1, U4.11 (4Y)
RPWM4_5V: J9.8, U9.8 (3Y)
RPWM5: U1.10 (8_TX2_IN1), U6.2 (1B), U10.2 (1A)
RPWM5BLINK: R39.1, R42.1, U6.3 (1Y)
RPWM5_5V: J10.8, U10.3 (1Y)
RPWM6: U1.12 (10_CS_MQSR), U6.13 (4B), U10.12 (4A)
RPWM6BLINK: R67.1, R70.1, U6.11 (4Y)
RPWM6_5V: J11.8, U10.11 (4Y)
RPWM7: U1.14 (12_MISO_MQSL), U7.2 (1B), U12.2 (1A)
RPWM7BLINK: R41.1, R44.1, U7.3 (1Y)
RPWM7_5V: J12.8, U12.3 (1Y)
RPWM8: U1.36 (14_A0_TX3_SPDIF_OUT), U7.13 (4B), U12.12 (4A)
RPWM8BLINK: R43.1, R46.1, U7.11 (4Y)
RPWM8_5V: J13.8, U12.11 (4Y)
R_IS1: J6.4
R_IS2: J7.4
R_IS3: J8.4
R_IS4: J9.4
R_IS5: J10.4
R_IS6: J11.4
R_IS7: J12.4
R_IS8: J13.4
SCL: R79.2, U1.41 (19_A5_SCL), U8.SCL, U11.7 (SCL)
SDA: R82.2, U1.40 (18_A4_SDA), U8.SDA, U11.6 (SDA)

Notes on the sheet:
FRONT LEFT
PWM 5
LPWM 6
PWM1
LOGIC GATES
9-AXIS IMU
LED MUX
RPWM 3
PWM7
RPWM 5
LED DISPLAYS
3.3V to 5V LEVEL SHIFTERS
RPWM 7
LPWM 5
QUADRATURE
ADC
PWM
PWM 8
PWM4
PWM 2
MOUNT HOLES
LPWM 3
LPWM 7
555 Timer
MCU
RPWM 1
PWM 7
PWM ENABLED 5-8
PWM 1
PWM 3
PWM8
PWM 6
REAR RIGHT
REAR LEFT
PWM ENABLED LEDS
FRONT RIGHT
LPWM 8
LPWM 2
PWM2
PWM6

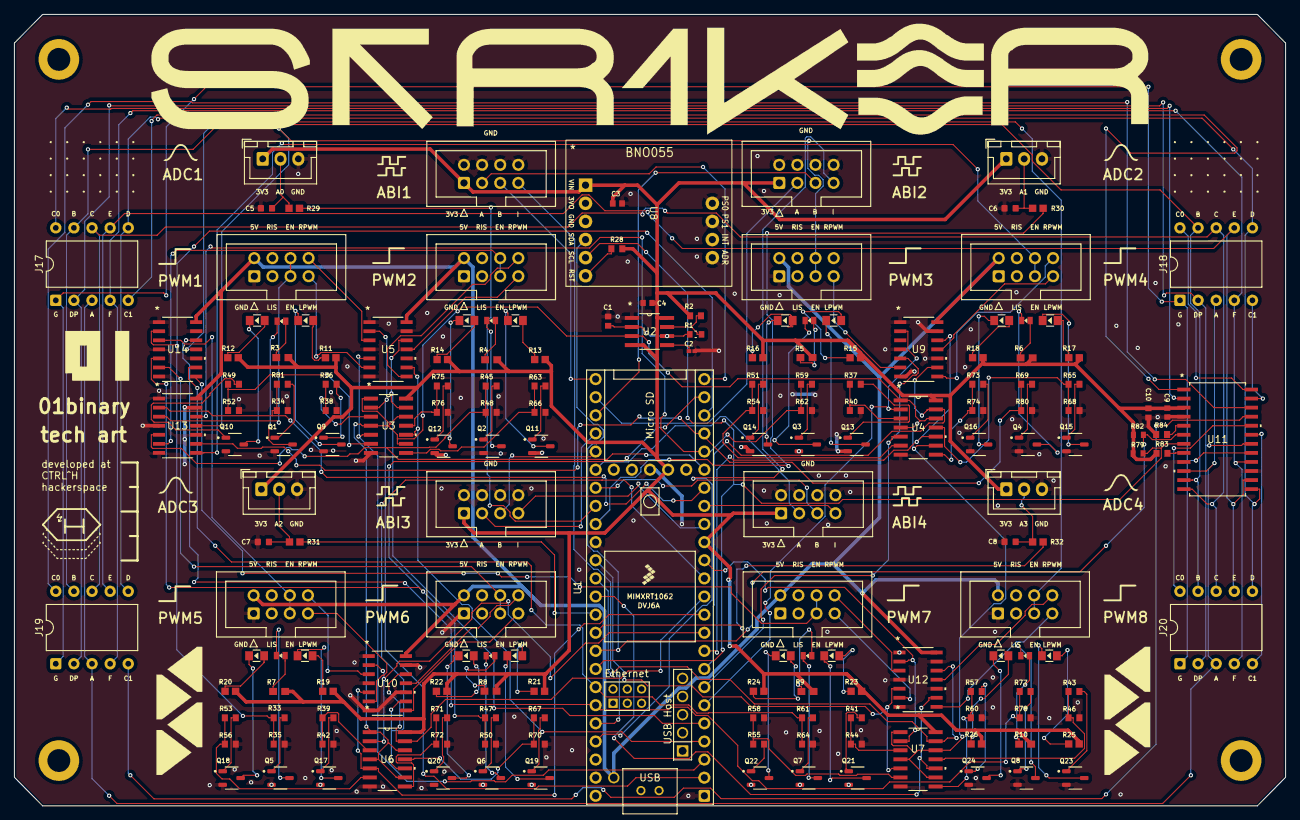
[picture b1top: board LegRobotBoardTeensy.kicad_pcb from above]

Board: 2 copper layers, 178.2 x 110.9 mm, 179 parts (0 on the bottom side), 183 nets.

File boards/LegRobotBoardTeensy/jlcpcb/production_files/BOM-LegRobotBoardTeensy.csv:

Comment,Designator,Footprint,LCSC,Quantity
100K,"R34,R35,R38,R40,R42,R44,R46,R48,R50,R52,R54,R56,R58,R60,R62,R64,R66,R68,R70,R72,R74,R76,R78,R80",CRCW0603100KFKEA,C844916,24
100nF,"C4,C9",CC0603KRX7R9BB104,C14663,2
10K,"R2,R28,R33,R36,R37,R39,R41,R43,R45,R47,R49,R51,R53,R55,R57,R59,R61,R63,R65,R67,R69,R71,R73,R75,R77,R81,R83",CRCW060310K0FKEA,C844918,27
10nF,C2,C0402C103J4RACTU,C2167451,1
150R,"R11,R12,R13,R14,R15,R16,R17,R18,R19,R20,R21,R22,R23,R24,R25,R26",RESC1607X60N,C114608,16
1uF,"C1,C10,C3",CC0603JRX7R7BB105,C519560,3
2.2K,"R29,R30,R31,R32",RC0603FR-072K2L,C114662,4
20K,R84,CRCW060310K0FKEA,C5123585,1
360K,R1,RC0603FR-07360KL,C137740,1
4.7K,"R79,R82",CR0603-FX-4701ELF,C17673,2
470R,"R10,R3,R4,R5,R6,R7,R8,R9",RC0603FR-07470RL,C114669,8
47nF,"C5,C6,C7,C8",CAPC1608X90N,C1622,4
74HCT125D,"U10,U12,U13,U14,U5,U9",74HCT125D,C5962,6
AO3400A,"Q1,Q10,Q11,Q12,Q13,Q14,Q15,Q16,Q17,Q18,Q19,Q2,Q20,Q21,Q22,Q23,Q24,Q3,Q4,Q5,Q6,Q7,Q8,Q9",AO3400A,C20917,24
BLUELED,"D10,D11,D12,D13,D14,D15,D16,D17,D18,D19,D20,D21,D22,D23,D24,D9",150080BS75000_Modified,C6067133,16
REDLED,"D1,D2,D3,D4,D5,D6,D7,D8",XL-1608SURC-06,C965799,8
SN74HC08DR,"U3,U4,U6,U7",SN74HC08DR,C337768,4
TLC555CDR,U2,TLC555CDR,C6986,1
Teensy4.1,U1,Teensy41,,1
IS31FL3739-GRLS4-TR,U11,IS31FL3730-QFLS2-TR,,1
